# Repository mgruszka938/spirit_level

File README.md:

# Digital Spirit Level 

A compact, battery-powered digital level built with an STM32 microcontroller and an OLED screen. This project was developed as part of the "Sensors in Embedded Applications" course at AGH University of Science and Technology.

## Project Overview
The goal was to design a highly portable, precise digital measuring tool. The device features a USB-C port for charging, built-in Li-Ion battery support, and a three-button interface for resetting or zeroing the position. 

## Hardware & Components
The component selection prioritizes low power consumption, accuracy, and a small physical footprint.

* **Microcontroller:** STM32L433 (ARM Cortex-M4) - Picked for its low power usage and built-in FPU (Floating Point Unit) for faster angle calculations. It also runs without an external crystal oscillator, saving board space.
* **IMU Sensor:** LSM6DSO - A 6-axis accelerometer/gyroscope chosen for its high stability and low noise. Communicates over I2C.
* **Power Management:** MCP73871 - A load-sharing charge controller. It allows the device to be used normally while the Li-Ion battery is charging.
* **Display:** 0.96-inch OLED - A small, high-contrast I2C screen for the user interface.
* **Connectivity:** USB-C (charging) and SWD (programming).

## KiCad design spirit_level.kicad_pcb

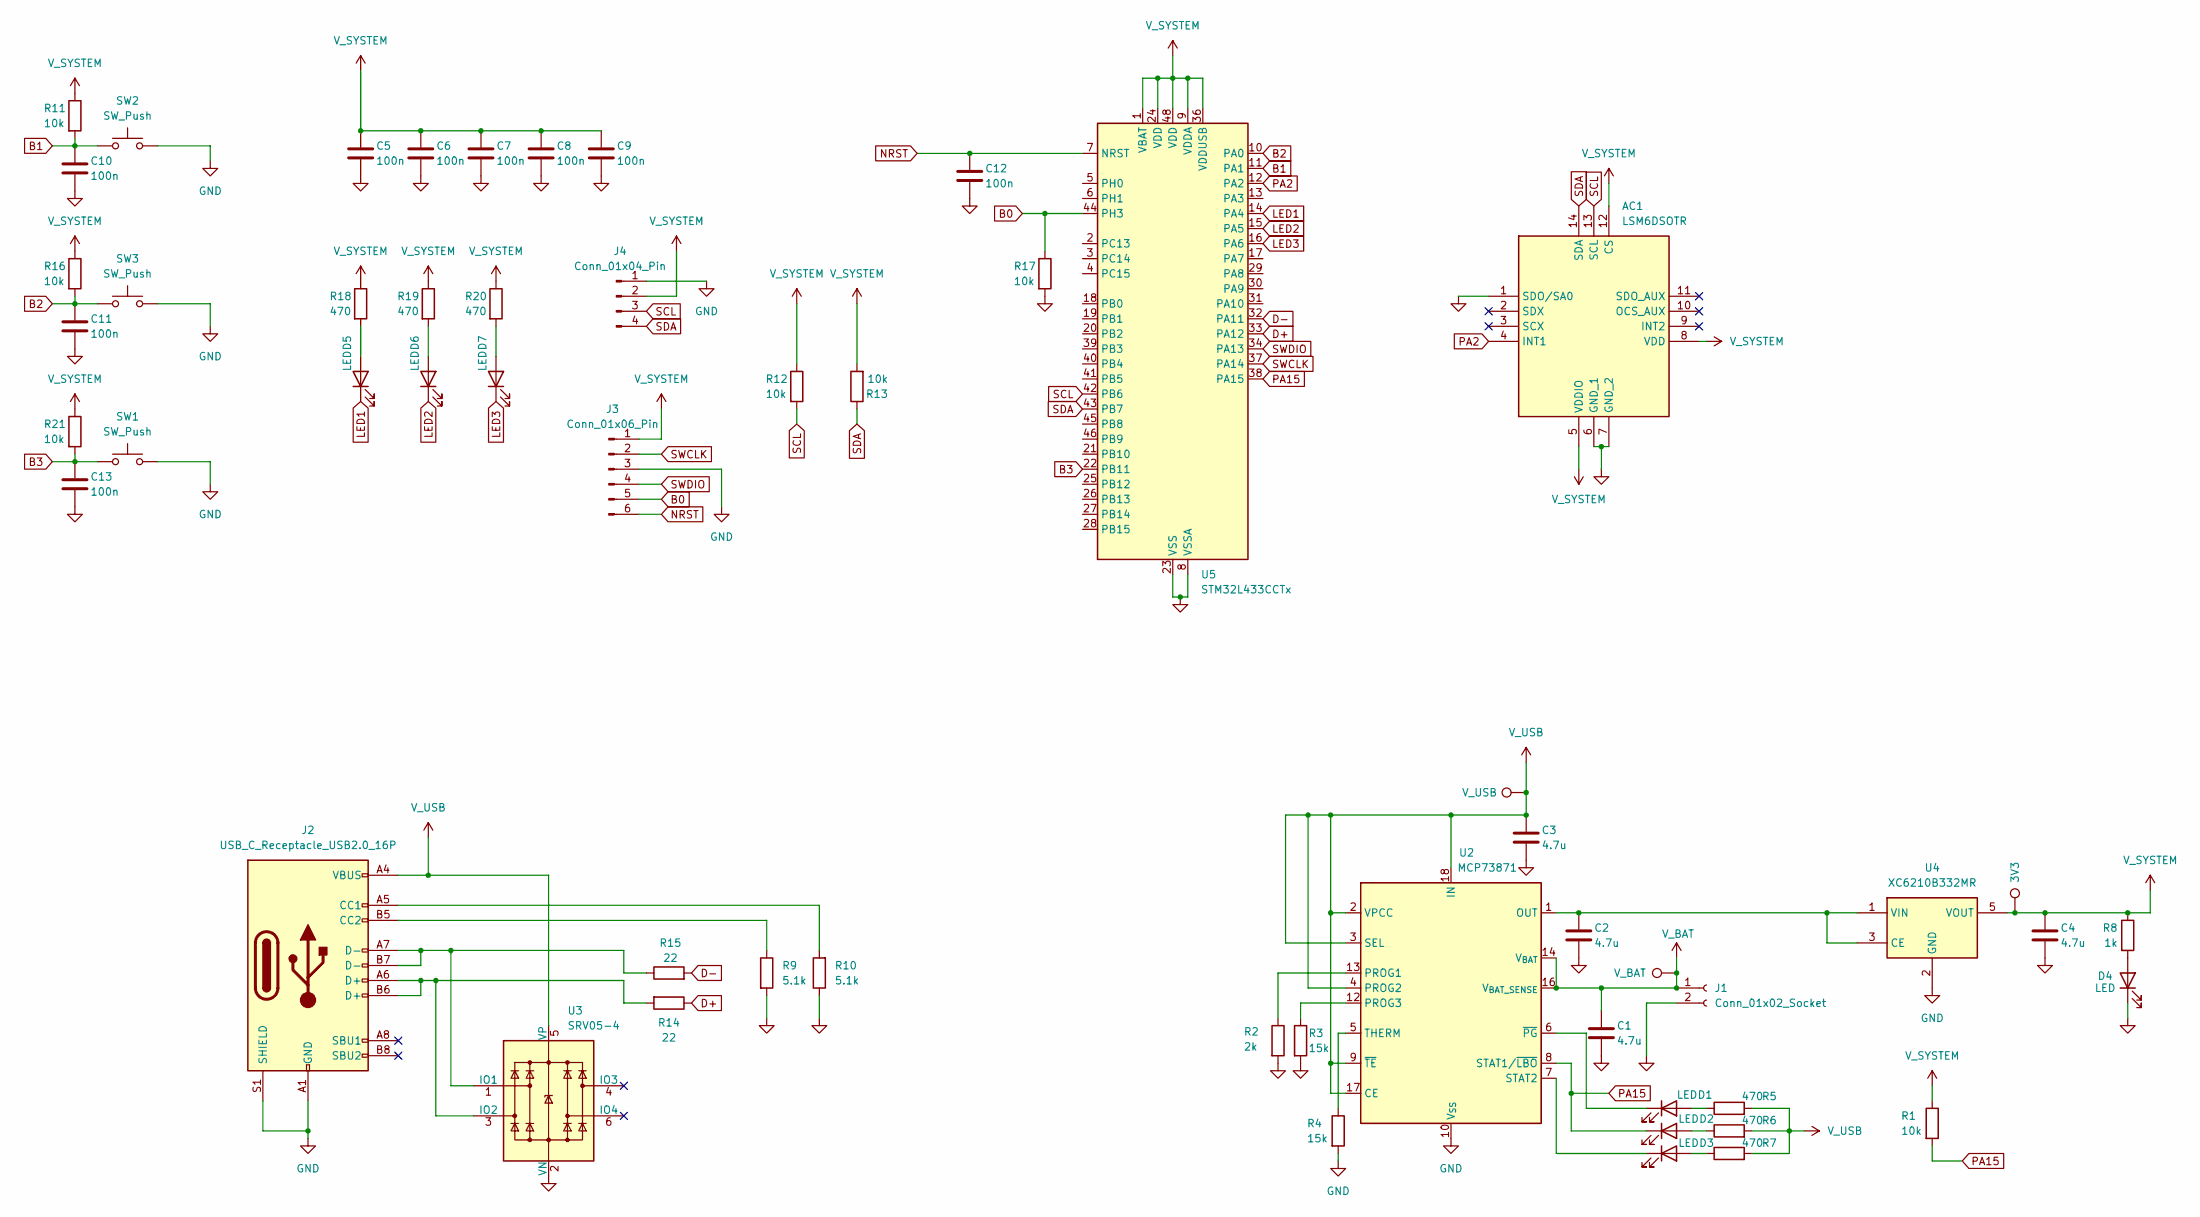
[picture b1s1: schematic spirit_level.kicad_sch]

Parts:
3V3: TestPoint_Pad_1.0x1.0mm
AC1: LSM6DSOTR; Mouser Part Number 511-LSM6DSOTR
C1, C2, C3, C4: 4.7u; C_0603_1608Metric_Pad1.08x0.95mm_HandSolder
C5, C6, C7, C8, C9, C10, C11, C12, C13: 100n; C_0603_1608Metric_Pad1.08x0.95mm_HandSolder
D1, D2, D3, D4, D5, D6, D7: LED; D_0603_1608Metric_Pad1.05x0.95mm_HandSolder
J1: Conn_01x02_Socket; JST_PH_B2B-PH-K_1x02_P2.00mm_Vertical
J2: USB_C_Receptacle_USB2.0_16P; USB_C_Receptacle_GCT_USB4105-xx-A_16P_TopMnt_Horizontal
J3: Conn_01x06_Pin; PinHeader_1x06_P2.54mm_Vertical
J4: Conn_01x04_Pin; PinHeader_1x04_P2.54mm_Vertical
R1, R11, R12, R13, R16, R17, R21: 10k; R_0603_1608Metric_Pad0.98x0.95mm_HandSolder
R2: 2k; R_0603_1608Metric_Pad0.98x0.95mm_HandSolder
R3, R4: 15k; R_0603_1608Metric_Pad0.98x0.95mm_HandSolder
R5, R6, R7, R18, R19, R20: 470; R_0603_1608Metric_Pad0.98x0.95mm_HandSolder
R8: 1k; R_0603_1608Metric_Pad0.98x0.95mm_HandSolder
R9, R10: 5.1k; R_0402_1005Metric_Pad0.72x0.64mm_HandSolder
R14, R15: 22; R_0603_1608Metric_Pad0.98x0.95mm_HandSolder
SW1, SW2, SW3: SW_Push; SW_SPST_PTS645Sx43SMTR92
U2: MCP73871; QFN-20-1EP_4x4mm_P0.5mm_EP2.5x2.5mm
U3: SRV05-4; SOT-23-6
U4: XC6210B332MR; SOT-23-5
U5: STM32L433CCTx; LQFP-48_7x7mm_P0.5mm
V_BAT: TestPoint_Pad_1.0x1.0mm
V_USB: TestPoint_Pad_1.0x1.0mm

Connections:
B0: J3.5, R17.1, U5.44 (PH3)
B1: C10.1, R11.2, SW2.1, U5.11 (PA1)
B2: C11.1, R16.2, SW3.1, U5.10 (PA0)
B3: C13.1, R21.2, SW1.1, U5.22 (PB11)
D+: R14.1, U5.33 (PA12)
D-: R15.2, U5.32 (PA11)
GND: AC1.1 (SDO/SA0), AC1.6 (GND_1), AC1.7 (GND_2), C1.2, C2.2, C3.2, C4.2, C5.2, C6.2, C7.2, C8.2, C9.2, C10.2, C11.2, C12.2, C13.2, D4.1 (K), J1.2, J2.A1 (GND), J2.A12 (GND), J2.B1 (GND), J2.B12 (GND), J2.S1 (SHIELD), J3.3, J4.1, R2.2, R3.2, R4.2, R9.2, R10.1, R17.2, SW1.2, SW2.2, SW3.2, U2.10 (V_{SS}), U2.11 (V_{SS}), U2.21 (V_{SS}), U3.2 (VN), U4.2 (GND), U5.8 (VSSA), U5.23 (VSS), U5.35 (VSS), U5.47 (VSS)
LED1: D5.1 (K), U5.14 (PA4)
LED2: D6.1 (K), U5.15 (PA5)
LED3: D7.1 (K), U5.16 (PA6)
NRST: C12.1, J3.6, U5.7 (NRST)
unnamed: D1.2 (A), R5.1
unnamed: D1.1 (K), U2.6 (~PG)
unnamed: D2.2 (A), R6.1
unnamed: D3.2 (A), R7.1
unnamed: D3.1 (K), U2.7 (STAT2)
unnamed: D4.2 (A), R8.2
unnamed: D5.2 (A), R18.2
unnamed: D6.2 (A), R19.2
unnamed: D7.2 (A), R20.2
unnamed: J2.A5 (CC1), R10.2
unnamed: J2.B5 (CC2), R9.1
unnamed: R2.1, U2.13 (PROG1)
unnamed: R3.1, U2.12 (PROG3)
unnamed: R4.1, U2.5 (THERM)
unnamed: J2.A7 (D-), J2.B7 (D-), R15.1, U3.1 (IO1)
unnamed: J2.A6 (D+), J2.B6 (D+), R14.2, U3.3 (IO2)
unnamed: C2.1, U2.1 (OUT), U2.20 (OUT), U4.1 (VIN), U4.3 (CE)
PA2: AC1.4 (INT1), U5.12 (PA2)
PA15: D2.1 (K), R1.2, U2.8 (STAT1/~LBO), U5.38 (PA15)
SCL: AC1.13 (SCL), J4.3, R12.2, U5.42 (PB6)
SDA: AC1.14 (SDA), J4.4, R13.1, U5.43 (PB7)
SWCLK: J3.2, U5.37 (PA14)
SWDIO: J3.4, U5.34 (PA13)
V_BAT: C1.1, J1.1, U2.14 (V_{BAT}), U2.15 (V_{BAT}), U2.16 (V_{BAT_SENSE}), V_BAT.1
V_SYSTEM: 3V3.1, AC1.5 (VDDIO), AC1.8 (VDD), AC1.12 (CS), C4.1, C5.1, C6.1, C7.1, C8.1, C9.1, J3.1, J4.2, R1.1, R8.1, R11.1, R12.1, R13.2, R16.1, R18.1, R19.1, R20.1, R21.1, U4.5 (VOUT), U5.1 (VBAT), U5.9 (VDDA), U5.24 (VDD), U5.36 (VDDUSB), U5.48 (VDD)
V_USB: C3.1, J2.A4 (VBUS), J2.A9 (VBUS), J2.B4 (VBUS), J2.B9 (VBUS), R5.2, R6.2, R7.2, U2.2 (VPCC), U2.3 (SEL), U2.4 (PROG2), U2.9 (~TE), U2.17 (CE), U2.18 (IN), U2.19 (IN), U3.5 (VP), V_USB.1

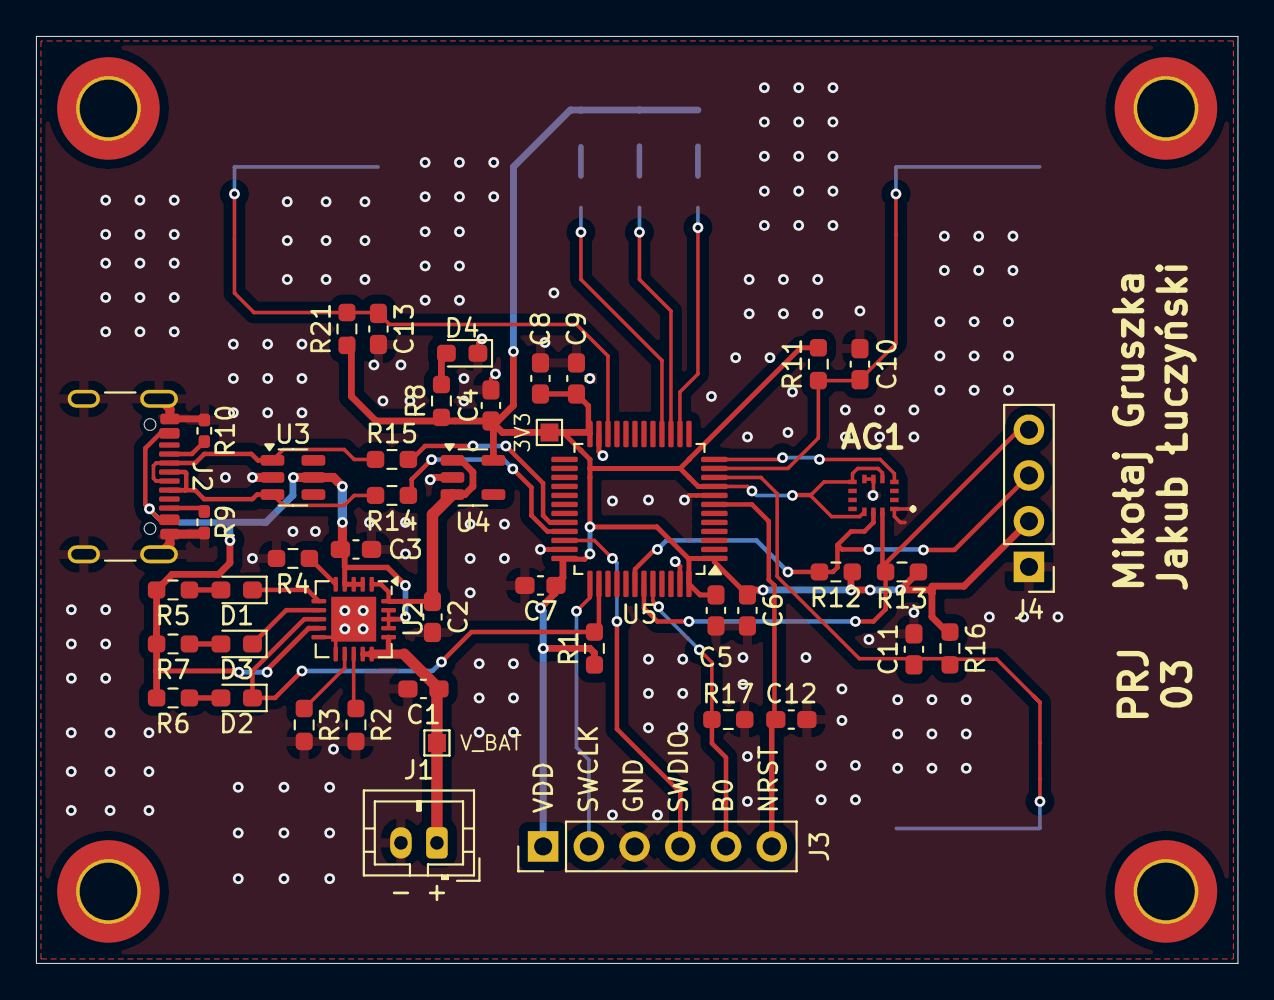
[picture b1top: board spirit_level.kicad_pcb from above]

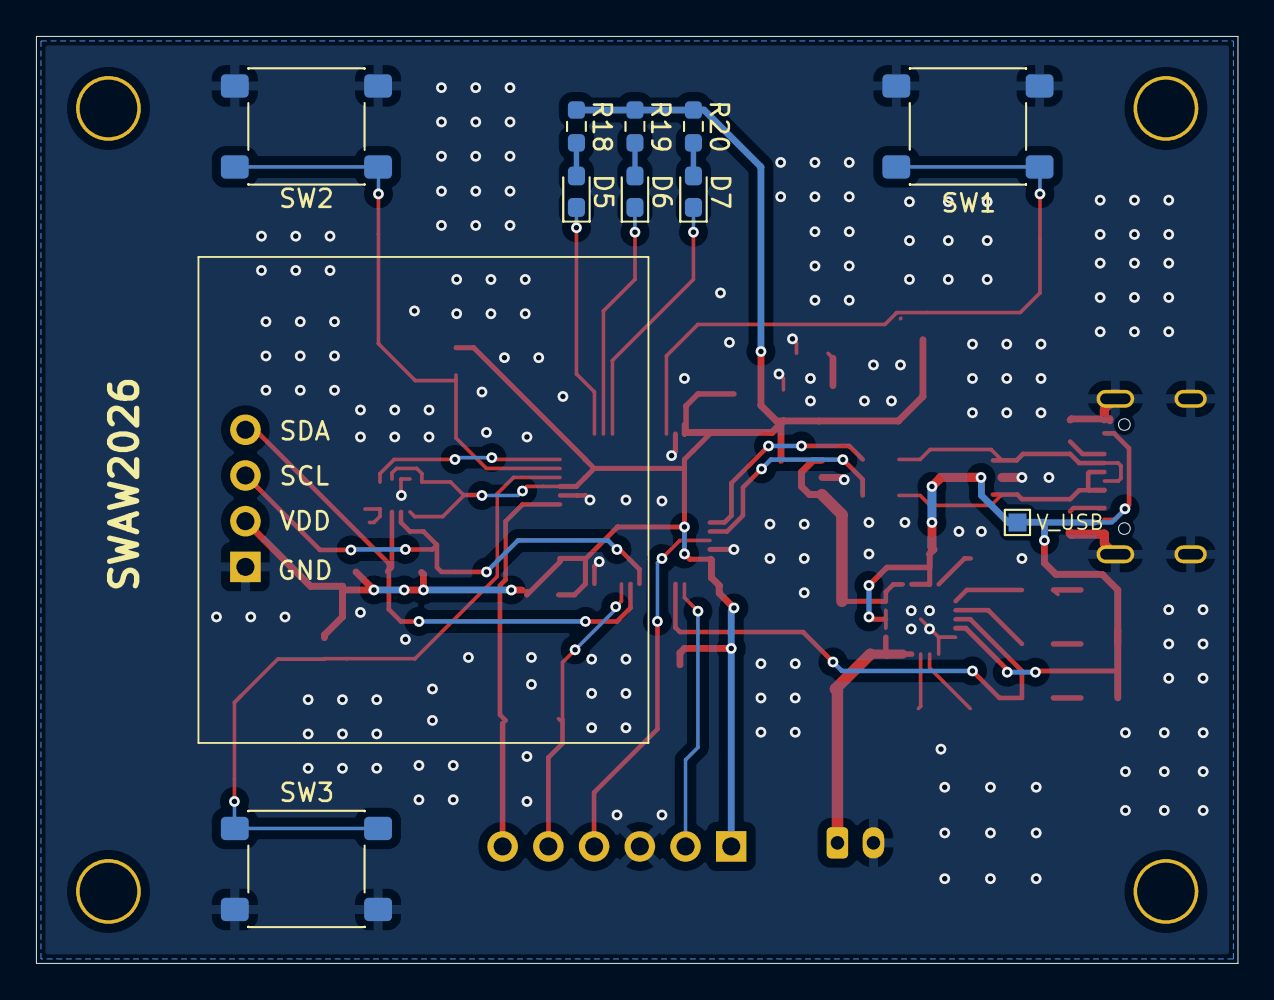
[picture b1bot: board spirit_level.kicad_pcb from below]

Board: 2 copper layers, 66.8 x 51.5 mm, 56 parts (10 on the bottom side), 37 nets.
